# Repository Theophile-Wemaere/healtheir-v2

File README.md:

# HEALTH-EIR v2.0

Arduino lib :
https://github.com/g200kg/kicad-lib-arduino

```
Problemes :
- footprints for headers are not standards
- there was a problem on the RX-TX communication between rpi and arduino, resulting in the rpi frying 

```

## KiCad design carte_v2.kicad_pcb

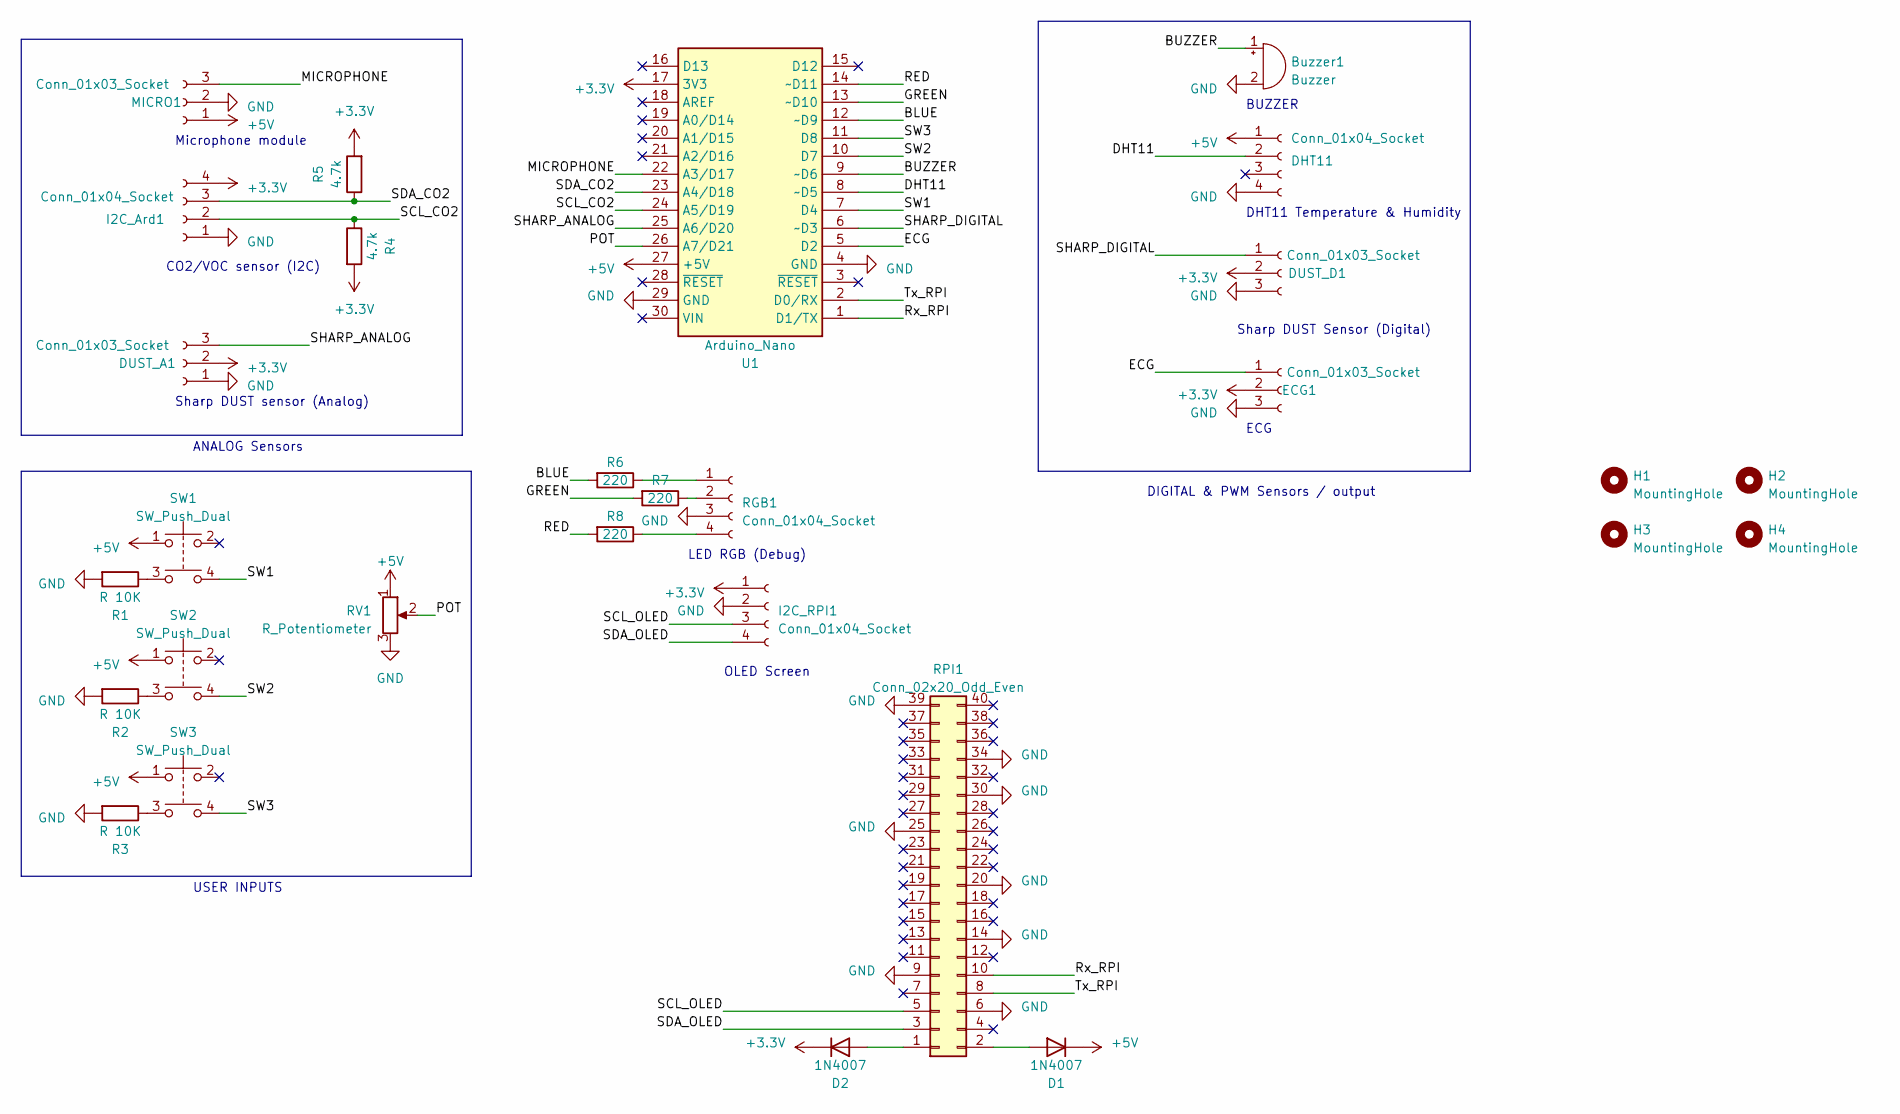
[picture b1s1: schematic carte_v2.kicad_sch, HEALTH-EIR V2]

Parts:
Buzzer1: Buzzer; Buzzer_15x7.5RM7.6
D1, D2: 1N4007; D_DO-41_SOD81_P10.16mm_Horizontal
DHT11: Conn_01x04_Socket; PinHeader_1x04_P2.00mm_Vertical
DUST_A1: Conn_01x03_Socket; PinHeader_1x03_P2.00mm_Vertical
DUST_D1: Conn_01x03_Socket; PinHeader_1x03_P2.00mm_Vertical
ECG1: Conn_01x03_Socket; PinHeader_1x03_P2.00mm_Vertical
H1, H2, H3, H4: MountingHole; MountingHole_3mm
I2C_Ard1, I2C_RPI1: Conn_01x04_Socket; PinHeader_1x04_P2.00mm_Vertical
MICRO1: Conn_01x03_Socket; PinHeader_1x03_P2.00mm_Vertical
R1, R2, R3: R 10K; R_Axial_DIN0204_L3.6mm_D1.6mm_P7.62mm_Horizontal
R4, R5: 4.7k; R_Axial_DIN0204_L3.6mm_D1.6mm_P7.62mm_Horizontal
R6, R7, R8: 220; R_Axial_DIN0204_L3.6mm_D1.6mm_P7.62mm_Horizontal
RGB1: Conn_01x04_Socket; PinHeader_1x04_P2.00mm_Vertical
RPI1: Conn_02x20_Odd_Even; PinHeader_2x20_P2.54mm_Vertical
RV1: R_Potentiometer; Potentiometer_Runtron_RM-065_Vertical
SW1, SW2, SW3: SW_Push_Dual; SW_PUSH_6mm_H5mm_PATCHED
U1: Arduino_Nano

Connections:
+3.3V: D2.1 (K), DUST_A1.2, DUST_D1.2, ECG1.2, I2C_Ard1.4, I2C_RPI1.1, R4.2, R5.2, U1.17 (3V3)
+5V: D1.1 (K), DHT11.1, MICRO1.1, RV1.1, SW1.1, SW2.1, SW3.1, U1.27 (+5V)
/BLUE: R6.2, U1.12 (~D9)
/BUZZER: Buzzer1.1 (-), U1.9 (~D6)
/DHT11: DHT11.2, U1.8 (~D5)
/ECG: ECG1.1, U1.5 (D2)
/GREEN: R7.2, U1.13 (~D10)
/MICROPHONE: MICRO1.3, U1.22 (A3/D17)
/POT: RV1.2, U1.26 (A7/D21)
/RED: R8.2, U1.14 (~D11)
/Rx_RPI: RPI1.10, U1.1 (D1/TX)
/SCL_CO2: I2C_Ard1.2, R4.1, U1.24 (A5/D19)
/SCL_OLED: I2C_RPI1.3, RPI1.5
/SDA_CO2: I2C_Ard1.3, R5.1, U1.23 (A4/D18)
/SDA_OLED: I2C_RPI1.4, RPI1.3
/SHARP_ANALOG: DUST_A1.3, U1.25 (A6/D20)
/SHARP_DIGITAL: DUST_D1.1, U1.6 (~D3)
/SW1: SW1.4, U1.7 (D4)
/SW2: SW2.4, U1.10 (D7)
/SW3: SW3.4, U1.11 (D8)
/Tx_RPI: RPI1.8, U1.2 (D0/RX)
GND: Buzzer1.2 (+), DHT11.4, DUST_A1.1, DUST_D1.3, ECG1.3, I2C_Ard1.1, I2C_RPI1.2, MICRO1.2, R1.2, R2.2, R3.2, RGB1.3, RPI1.6, RPI1.9, RPI1.14, RPI1.20, RPI1.25, RPI1.30, RPI1.34, RPI1.39, RV1.3, U1.4 (GND), U1.29 (GND)
unnamed: D1.2 (A), RPI1.2
unnamed: D2.2 (A), RPI1.1
unnamed: R1.1, SW1.3
unnamed: R2.1, SW2.3
unnamed: R3.1, SW3.3
unnamed: R6.1, RGB1.1
unnamed: R7.1, RGB1.2
unnamed: R8.1, RGB1.4

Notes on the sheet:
USER INPUTS
Sharp DUST sensor (Analog)
Microphone module
OLED Screen
DHT11 Temperature & Humidity
DIGITAL & PWM Sensors / output
BUZZER
LED RGB (Debug)
ECG
Sharp DUST Sensor (Digital)
CO2/VOC sensor (I2C)
ANALOG Sensors

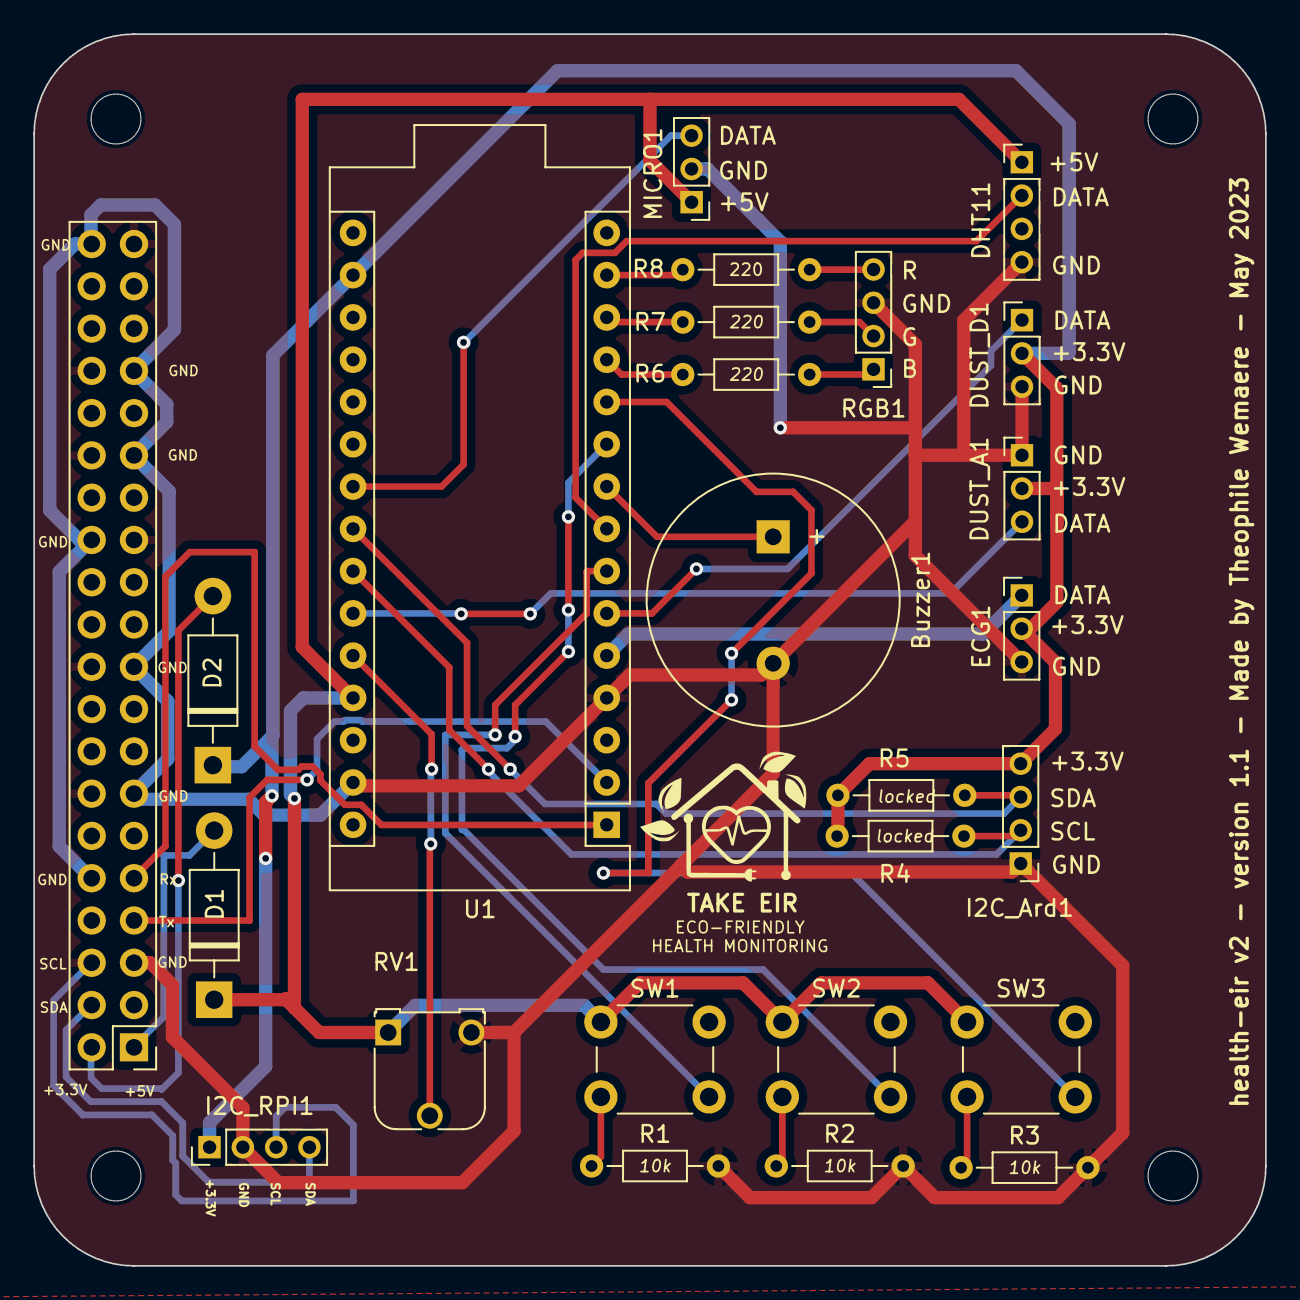
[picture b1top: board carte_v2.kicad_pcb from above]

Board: 2 copper layers, 74.0 x 74.0 mm, 29 parts (0 on the bottom side), 30 nets.

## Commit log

2023-05-01 created repo
2023-05-01 added user input + sensors
2023-05-01 added rgb leds + reworked buzzer
2023-05-01 added raspberry GPIO + resitor
2023-05-02 added resistor + began routing
2023-05-02 almost finished routing (missing buttons)
2023-05-05 routing finished, need to resolve error
2023-05-07 added imgs
2023-05-22 created fabrications files
2023-05-22 added mouting hole + routing over with no error
2023-05-22 remake rpi footprint
2023-06-22 added 3D models
